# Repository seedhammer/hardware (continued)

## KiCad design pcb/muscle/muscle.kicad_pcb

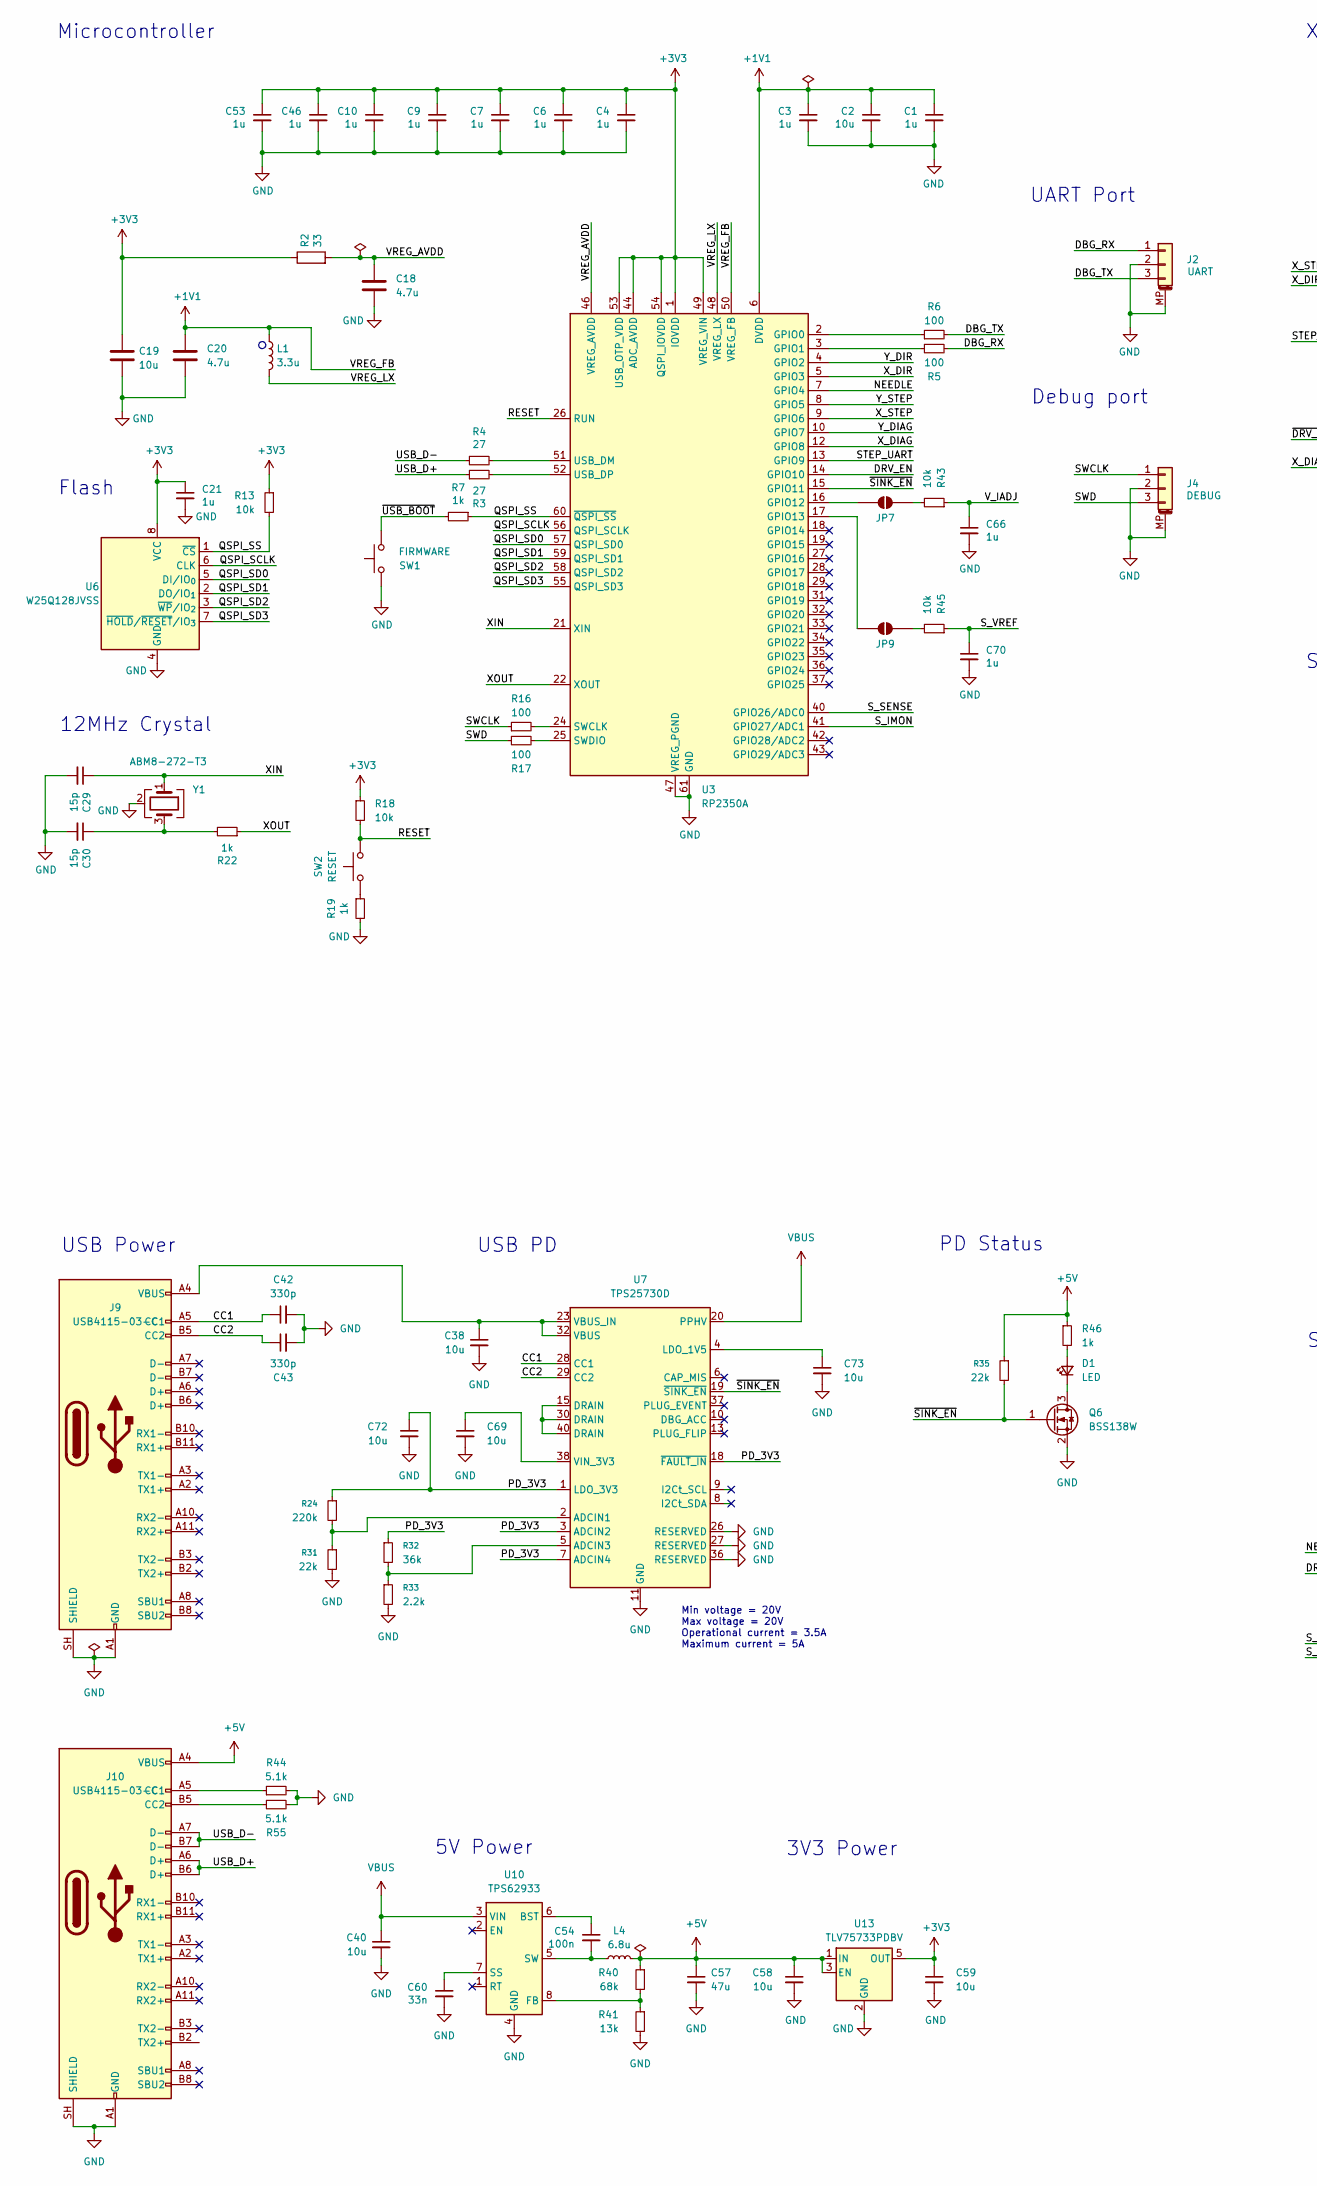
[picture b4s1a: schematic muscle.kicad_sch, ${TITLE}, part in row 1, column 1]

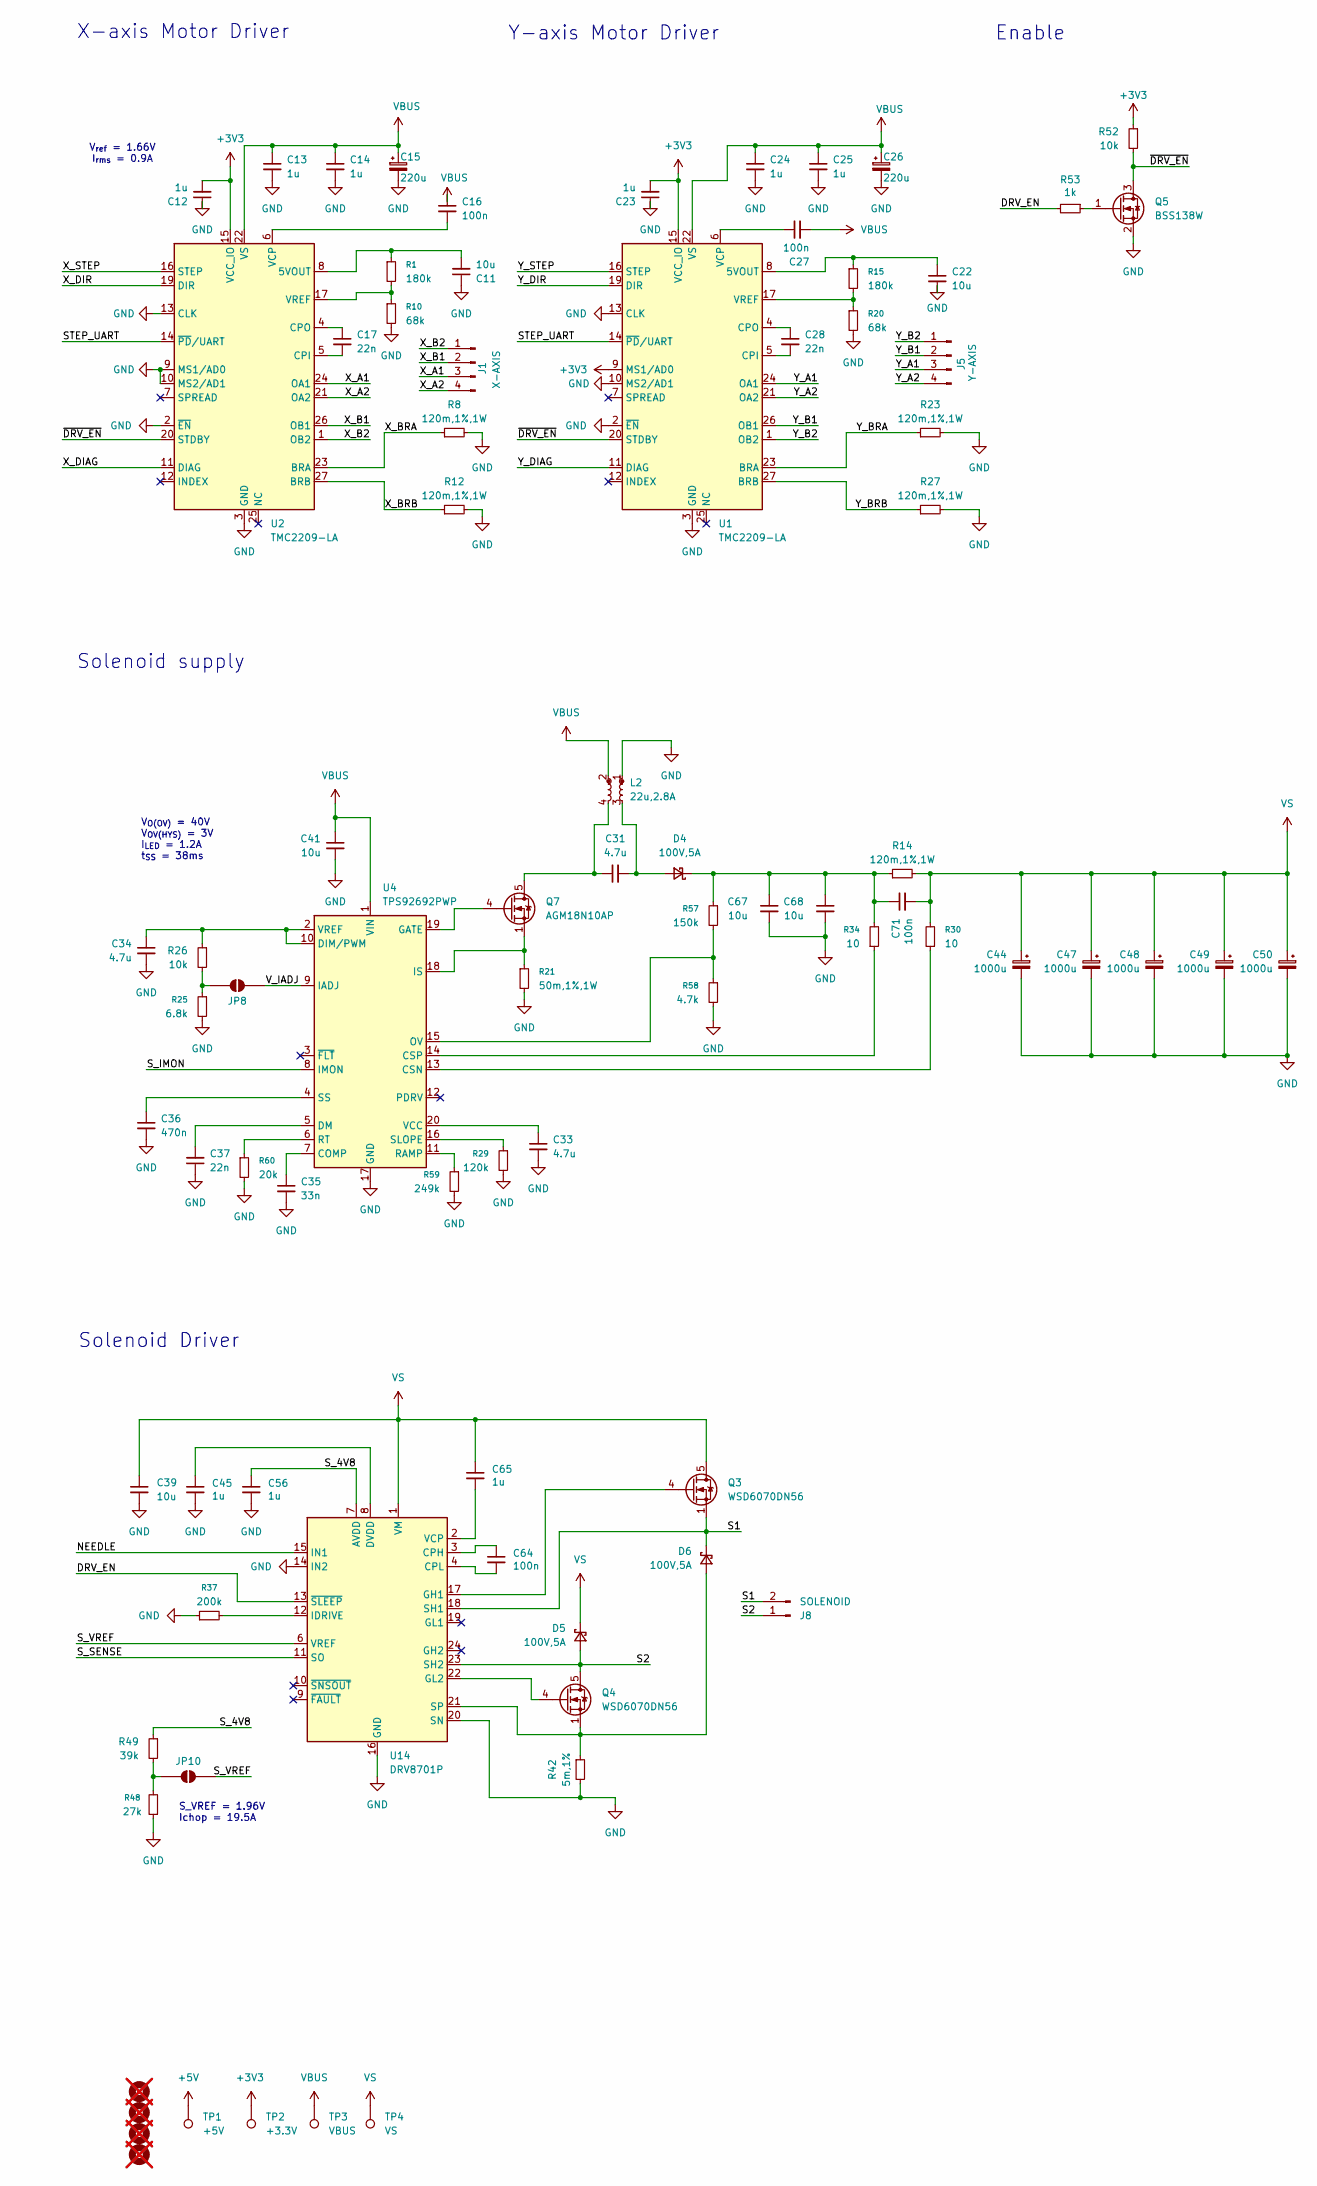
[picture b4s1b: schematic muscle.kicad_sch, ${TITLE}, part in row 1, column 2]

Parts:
C1, C3, C4, C6, C7, C9, C10, C12, C21, C23, C45, C46, C53, C56, C66, C70: 1u; C_0402_1005Metric; LCSC C52923
C2, C11, C22, C58, C59, C69, C72, C73: 10u; C_0402_1005Metric; LCSC C15525
C13, C14, C24, C25, C65: 1u; C_0603_1608Metric; LCSC C15849
C15, C26: 220u; CP_Elec_8x10; LCSC C970697
C16, C27: 100n; C_0603_1608Metric; LCSC C14663
C17, C28, C37: 22n; C_0402_1005Metric; LCSC C1532
C18, C33, C34: 4.7u; C_0402_1005Metric; LCSC C23733
C19: 10u; C_0402_1005Metric_small_pads; LCSC C15525
C20: 4.7u; C_0402_1005Metric_small_pads; LCSC C23733
C29, C30: 15p; C_0402_1005Metric; LCSC C1548
C31: 4.7u; C_1206_3216Metric; LCSC C33546020
C35, C60: 33n; C_0603_1608Metric; LCSC C21117
C36: 470n; C_0603_1608Metric; LCSC C1623
C38, C40, C41: 10u; C_0603_1608Metric; LCSC C96446
C39, C67, C68: 10u; C_1206_3216Metric; LCSC C13585
C42, C43: 330p; C_0603_1608Metric; LCSC C1664
C44, C47, C48, C49, C50: 1000u; CP_Radial_D13.0mm_P5.00mm; LCSC C18104
C54, C64, C71: 100n; C_0402_1005Metric; LCSC C307331
C57: 47u; C_1206_3216Metric; LCSC C96123
D1: LED; LED_0603_1608Metric; LCSC C2290
D4, D5, D6: 100V,5A; D_SMB; LCSC C41410776
H1, H2, H3, H4: MountingHole; MountingHole_3.2mm_M3_DIN965; not fitted
J1, J5: B4B-XH-2(LF)(SN); JST_XH_B4B-XH-A_1x04_P2.50mm_Vertical_Motor; LCSC C57846
J2, J4: ZX-SH1.0-3PLT; JST_SH_BM03B-SRSS-TB_1x03-1MP_P1.00mm_Vertical; LCSC C7430452
J8: B2B-XH-A(LF)(SN); JST_XH_B2B-XH-A_1x02_P2.50mm_Vertical; LCSC C24193
J9, J10: USB4115-03-C; USB_C_Receptacle_GCT_USB4115-03-C; LCSC C5250720
JP7, JP8, JP9, JP10: SolderJumper_2_Bridged; SolderJumper-2_P1.3mm_Open_Pad1.0x1.5mm
L1: 3.3u; L_pol_2016; LCSC C42411119
L2: 22u,2.8A; L_Bourns_SRF1260; LCSC C54563340
L4: 6.8u; L_Vishay_IFSC-1515AH_4x4x1.8mm; LCSC C843301
Q3, Q4: WSD6070DN56; WSD_DFN-8-1EP_6x5mm_P1.27mm_ThermalVias; LCSC C5772651
Q5, Q6: BSS138W; SOT-323_SC-70; LCSC C28646265
Q7: AGM18N10AP; VSON-8_3.3x3.3mm_P0.65mm_NexFET; LCSC C7509649
R1, R15: 180k; R_0603_1608Metric; LCSC C22827
R2: 33; R_0402_1005Metric; LCSC C25105
R3, R4: 27; R_0402_1005Metric; LCSC C25100
R5, R6, R16, R17: 100; R_0402_1005Metric; LCSC C25076
R7, R19, R22, R46, R53: 1k; R_0402_1005Metric; LCSC C11702
R8, R12, R14, R23, R27: 120m,1%,1W; R_1206_3216Metric; LCSC C201309
R10, R20: 68k; R_0402_1005Metric; LCSC C23231
R13, R18, R26, R43, R45, R52: 10k; R_0402_1005Metric; LCSC C25744
R21: 50m,1%,1W; R_1206_3216Metric; LCSC C7467249
R24: 220k; R_0603_1608Metric; LCSC C22961
R25: 6.8k; R_0603_1608Metric; LCSC C23212
R29: 120k; R_0603_1608Metric; LCSC C25808
R30, R34: 10; R_0402_1005Metric; LCSC C25077
R31, R35: 22k; R_0402_1005Metric; LCSC C25768
R32: 36k; R_0603_1608Metric; LCSC C23147
R33: 2.2k; R_0402_1005Metric; LCSC C25879
R37: 200k; R_0402_1005Metric; LCSC C25764
R40: 68k; R_0603_1608Metric; LCSC C23231
R41: 13k; R_0603_1608Metric; LCSC C22797
R42: 5m,1%; R_0805_2012Metric; LCSC C728267
R44, R55: 5.1k; R_0402_1005Metric; LCSC C25905
R48: 27k; R_0603_1608Metric; LCSC C22967
R49: 39k; R_0603_1608Metric; LCSC C23153
R57: 150k; R_0603_1608Metric; LCSC C22807
R58: 4.7k; R_0402_1005Metric; LCSC C25900
R59: 249k; R_0402_1005Metric; LCSC C226368
R60: 20k; R_0402_1005Metric; LCSC C25765
SW1, SW2: TS3425BA; SW_Push_1P1T_NO_Vertical_Wuerth_434133025816; LCSC C2681476
TP1: +5V; TestPoint_Pad_1.5x1.5mm
TP2: +3.3V; TestPoint_Pad_1.5x1.5mm
TP3: VBUS; TestPoint_Pad_1.5x1.5mm
TP4: VS; TestPoint_Pad_1.5x1.5mm
U1, U2: TMC2209-LA; VQFN-28-1EP_5x5mm_P0.5mm_EP3.7x3.7mm_ThermalVias; LCSC C2150710
U3: RP2350A; QFN-60-1EP_7x7mm_P0.4mm_EP3.4x3.4mm_ThermalVias; LCSC C42411118
U4: TPS92692PWP; HTSSOP-20-1EP_4.4x6.5mm_P0.65mm_EP3.4x6.5mm_Mask2.75x3.43mm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; LCSC C111084
U6: W25Q128JVSS; SOIC-8_5.3x5.3mm_P1.27mm; LCSC C97521
U7: TPS25730D; Texas_REF0038A_WQFN-38-2EP_6x4mm_P0.4; LCSC C22438973
U10: TPS62933; SOT-583-8; LCSC C3200405
U13: TLV75733PDBV; SOT-23-5; LCSC C485517
U14: DRV8701P; VQFN-24-1EP_4x4mm_P0.5mm_EP2.45x2.45mm_ThermalVias; LCSC C114178
Y1: ABM8-272-T3; Crystal_SMD_3225-4Pin_3.2x2.5mm; LCSC C20625731

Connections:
+1V1: C1.1, C2.1, C3.1, C20.1, L1.1, U3.6 (DVDD), U3.23 (DVDD), U3.39 (DVDD), U3.50 (VREG_FB)
+3V3: C4.1, C6.1, C7.1, C9.1, C10.1, C12.2, C19.1, C21.1, C23.2, C46.1, C53.1, C59.1, R2.1, R13.1, R18.1, R52.1, TP2.1 (1_1), U1.9 (MS1/AD0), U1.15 (VCC_IO), U2.15 (VCC_IO), U3.1 (IOVDD), U3.11 (IOVDD), U3.20 (IOVDD), U3.30 (IOVDD), U3.38 (IOVDD), U3.44 (ADC_AVDD), U3.45 (IOVDD), U3.49 (VREG_VIN), U3.53 (USB_OTP_VDD), U3.54 (QSPI_IOVDD), U6.8 (VCC), U13.5 (OUT)
+5V: C57.1, C58.1, J10.A4 (VBUS), J10.A9 (VBUS), J10.B4 (VBUS), J10.B9 (VBUS), L4.2, R35.1, R40.1, R46.1, TP1.1 (1_1), U13.1 (IN), U13.3 (EN)
/CC1: C42.1, J9.A5 (CC1), U7.28 (CC1)
/CC2: C43.1, J9.B5 (CC2), U7.29 (CC2)
/DBG_RX: J2.1, R5.2
/DBG_TX: J2.3, R6.2
/DRV_EN: R53.2, U3.14 (GPIO10), U14.13 (~SLEEP)
/NEEDLE: U3.7 (GPIO4), U14.15 (IN1)
/PD_3V3: C72.1, R24.1, R32.1, U7.1 (LDO_3V3), U7.3 (ADCIN2), U7.7 (ADCIN4), U7.18 (~FAULT_IN)
/QSPI_SCLK: U3.56 (QSPI_SCLK), U6.6 (CLK)
/QSPI_SD0: U3.57 (QSPI_SD0), U6.5 (DI/IO_{0})
/QSPI_SD1: U3.59 (QSPI_SD1), U6.2 (DO/IO_{1})
/QSPI_SD2: U3.58 (QSPI_SD2), U6.3 (~WP/IO_{2})
/QSPI_SD3: U3.55 (QSPI_SD3), U6.7 (~HOLD/~RESET/IO_{3})
/QSPI_SS: R7.1, R13.2, U3.60 (~QSPI_SS), U6.1 (~CS)
/RESET: R18.2, SW2.2, U3.26 (RUN)
/S1: D6.1 (K), J8.2, Q3.1 (S), Q3.2 (S), Q3.3 (S), U14.18 (SH1)
/S2: D5.2 (A), J8.1, Q4.5 (D), U14.23 (SH2)
/STEP_UART: U1.14 (~PD/UART), U2.14 (~PD/UART), U3.13 (GPIO9)
/SWCLK: J4.1, R16.1
/SWD: J4.3, R17.1
/S_4V8: C56.1, R49.1, U14.7 (AVDD)
/S_IMON: U3.41 (GPIO27/ADC1), U4.8 (IMON)
/S_SENSE: U3.40 (GPIO26/ADC0), U14.11 (SO)
/S_VREF: C70.1, JP10.1 (A), R45.1, U14.6 (VREF)
/USB_D+: J10.A6 (D+), J10.B6 (D+), R3.1
/USB_D-: J10.A7 (D-), J10.B7 (D-), R4.1
/VREG_AVDD: C18.1, R2.2, U3.46 (VREG_AVDD)
/VREG_LX: L1.2, U3.48 (VREG_LX)
/V_IADJ: C66.1, JP8.1 (A), R43.1, U4.9 (IADJ)
/XIN: C29.1, U3.21 (XIN), Y1.1
/XOUT: R22.1, U3.22 (XOUT)
/X_A1: J1.3, U2.24 (OA1)
/X_A2: J1.4, U2.21 (OA2)
/X_B1: J1.2, U2.26 (OB1)
/X_B2: J1.1, U2.1 (OB2)
/X_BRA: R8.1, U2.23 (BRA)
/X_BRB: R12.1, U2.27 (BRB)
/X_DIAG: U2.11 (DIAG), U3.12 (GPIO8)
/X_DIR: U2.19 (DIR), U3.5 (GPIO3)
/X_STEP: U2.16 (STEP), U3.9 (GPIO6)
/Y_A1: J5.3, U1.24 (OA1)
/Y_A2: J5.4, U1.21 (OA2)
/Y_B1: J5.2, U1.26 (OB1)
/Y_B2: J5.1, U1.1 (OB2)
/Y_BRA: R23.1, U1.23 (BRA)
/Y_BRB: R27.1, U1.27 (BRB)
/Y_DIAG: U1.11 (DIAG), U3.10 (GPIO7)
/Y_DIR: U1.19 (DIR), U3.4 (GPIO2)
/Y_STEP: U1.16 (STEP), U3.8 (GPIO5)
/~DRV_EN: Q5.3 (D), R52.2, U1.20 (STDBY), U2.20 (STDBY)
/~SINK_EN: Q6.1 (G), R35.2, U3.15 (GPIO11), U7.19 (~SINK_EN)
/~USB_BOOT: R7.2, SW1.1
GND: C1.2, C2.2, C3.2, C4.2, C6.2, C7.2, C9.2, C10.2, C11.1, C12.1, C13.2, C14.2, C15.2, C18.2, C19.2, C20.2, C21.2, C22.2, C23.1, C24.2, C25.2, C26.2, C29.2, C30.2, C33.2, C34.2, C35.2, C36.2, C37.1, C38.2, C39.2, C40.2, C41.2, C42.2, C43.2, C44.2, C45.2, C46.2, C47.2, C48.2, C49.2, C50.2, C53.2, C56.2, C57.2, C58.2, C59.2, C60.2, C66.2, C67.2, C68.2, C69.2, C70.2, C72.2, C73.2, J2.2, J2.MP (MountPin), J4.2, J4.MP (MountPin), J9.A1 (GND), J9.A12 (GND), J9.B1 (GND), J9.B12 (GND), J9.SH (SHIELD), J10.A1 (GND), J10.A12 (GND), J10.B1 (GND), J10.B12 (GND), J10.SH (SHIELD), L2.1, Q5.2 (S), Q6.2 (S), R8.2, R10.2, R12.2, R19.2, R20.2, R21.2, R23.2, R25.2, R27.2, R29.2, R31.2, R33.2, R37.1, R41.2, R42.2, R44.2, R48.1, R55.2, R58.2, R59.2, R60.2, SW1.2, U1.2 (~EN), U1.3 (GND), U1.10 (MS2/AD1), U1.13 (CLK), U1.18 (GND), U1.29 (GND), U2.2 (~EN), U2.3 (GND), U2.9 (MS1/AD0), U2.10 (MS2/AD1), U2.13 (CLK), U2.18 (GND), U2.29 (GND), U3.47 (VREG_PGND), U3.61 (GND), U4.17 (GND), U4.21 (GND), U6.4 (GND), U7.11 (GND), U7.12 (GND), U7.14 (GND), U7.16 (GND), U7.17 (GND), U7.26 (RESERVED), U7.27 (RESERVED), U7.31 (GND), U7.34 (GND), U7.36 (RESERVED), U7.39 (GND), U10.4 (GND), U13.2 (GND), U14.5 (GND), U14.14 (IN2), U14.16 (GND), U14.20 (SN), U14.25 (GND), Y1.2 (G), Y1.4 (G)
unnamed: C30.1, R22.2, Y1.3
unnamed: D1.2 (A), R46.2
unnamed: D1.1 (K), Q6.3 (D)
unnamed: C31.2, D4.2 (A), L2.3
unnamed: C67.1, C68.1, C71.1, D4.1 (K), R14.1, R34.2, R57.1
unnamed: D6.2 (A), Q4.1 (S), Q4.2 (S), Q4.3 (S), R42.1, U14.21 (SP)
unnamed: J10.A5 (CC1), R44.1
unnamed: J10.B5 (CC2), R55.1
unnamed: JP7.1 (A), R43.2
unnamed: JP7.2 (B), U3.16 (GPIO12)
unnamed: JP8.2 (B), R25.1, R26.2
unnamed: JP9.1 (A), R45.2
unnamed: JP9.2 (B), U3.17 (GPIO13)
unnamed: JP10.2 (B), R48.2, R49.2
unnamed: Q3.4 (G), U14.17 (GH1)
unnamed: Q4.4 (G), U14.22 (GL2)
unnamed: Q5.1 (G), R53.1
unnamed: C31.1, L2.4, Q7.5 (D)
unnamed: Q7.4 (G), U4.19 (GATE)
unnamed: R19.1, SW2.1
unnamed: C22.1, R15.1, U1.8 (5VOUT)
unnamed: C28.2, U1.5 (CPI)
unnamed: C28.1, U1.4 (CPO)
unnamed: C27.1, U1.6 (VCP)
unnamed: R15.2, R20.1, U1.17 (VREF)
unnamed: C11.2, R1.1, U2.8 (5VOUT)
unnamed: C17.2, U2.5 (CPI)
unnamed: C17.1, U2.4 (CPO)
unnamed: C16.2, U2.6 (VCP)
unnamed: R1.2, R10.1, U2.17 (VREF)
unnamed: R6.1, U3.2 (GPIO0)
unnamed: R5.1, U3.3 (GPIO1)
unnamed: R16.2, U3.24 (SWCLK)
unnamed: R17.2, U3.25 (SWDIO)
unnamed: R4.2, U3.51 (USB_DM)
unnamed: R3.2, U3.52 (USB_DP)
unnamed: C35.1, U4.7 (COMP)
unnamed: R30.1, U4.13 (CSN)
unnamed: R34.1, U4.14 (CSP)
unnamed: C34.1, R26.1, U4.2 (VREF), U4.10 (DIM/PWM)
unnamed: C37.2, U4.5 (DM)
unnamed: Q7.1 (S), Q7.2 (S), Q7.3 (S), R21.1, U4.18 (IS)
unnamed: R57.2, R58.1, U4.15 (OV)
unnamed: R59.1, U4.11 (RAMP)
unnamed: R60.1, U4.6 (RT)
unnamed: R29.1, U4.16 (SLOPE)
unnamed: C36.1, U4.4 (SS)
unnamed: C33.1, U4.20 (VCC)
unnamed: R24.2, R31.1, U7.2 (ADCIN1)
unnamed: R32.2, R33.1, U7.5 (ADCIN3)
unnamed: U7.15 (DRAIN), U7.30 (DRAIN), U7.40 (DRAIN)
unnamed: C73.1, U7.4 (LDO_1V5)
unnamed: C38.1, J9.A4 (VBUS), J9.A9 (VBUS), J9.B4 (VBUS), J9.B9 (VBUS), U7.23 (VBUS_IN), U7.32 (VBUS)
unnamed: C69.1, U7.38 (VIN_3V3)
unnamed: C54.1, U10.6 (BST)
unnamed: R40.2, R41.1, U10.8 (FB)
unnamed: C60.1, U10.7 (SS)
unnamed: C54.2, L4.1, U10.5 (SW)
unnamed: C64.1, U14.3 (CPH)
unnamed: C64.2, U14.4 (CPL)
unnamed: C45.1, U14.8 (DVDD)
unnamed: R37.2, U14.12 (IDRIVE)
unnamed: C65.2, U14.2 (VCP)
VBUS: C13.1, C14.1, C15.1, C16.1, C24.1, C25.1, C26.1, C27.2, C40.1, C41.1, L2.2, TP3.1 (1_1), U1.22 (VS), U1.28 (VS), U2.22 (VS), U2.28 (VS), U4.1 (VIN), U7.20 (PPHV), U10.3 (VIN)
VS: C39.1, C44.1, C47.1, C48.1, C49.1, C50.1, C65.1, C71.2, D5.1 (K), Q3.5 (D), R14.2, R30.2, TP4.1 (1_1), U14.1 (VM)

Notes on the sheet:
S_VREF = 1.96V Ichop = 19.5A
Solenoid supply
UART Port
USB Power
V_{O(OV)} = 40V V_{OV(HYS)} = 3V I_{LED} = 1.2A t_{SS} = 38ms
X-axis Motor Driver
Solenoid Driver
USB PD
5V Power
Debug port
V_{ref} = 1.66V I_{rms} = 0.9A
Y-axis Motor Driver
Min voltage = 20V Max voltage = 20V Operational current = 3.5A Maximum current = 5A
Microcontroller
12MHz Crystal
3V3 Power
PD Status
Flash
Enable

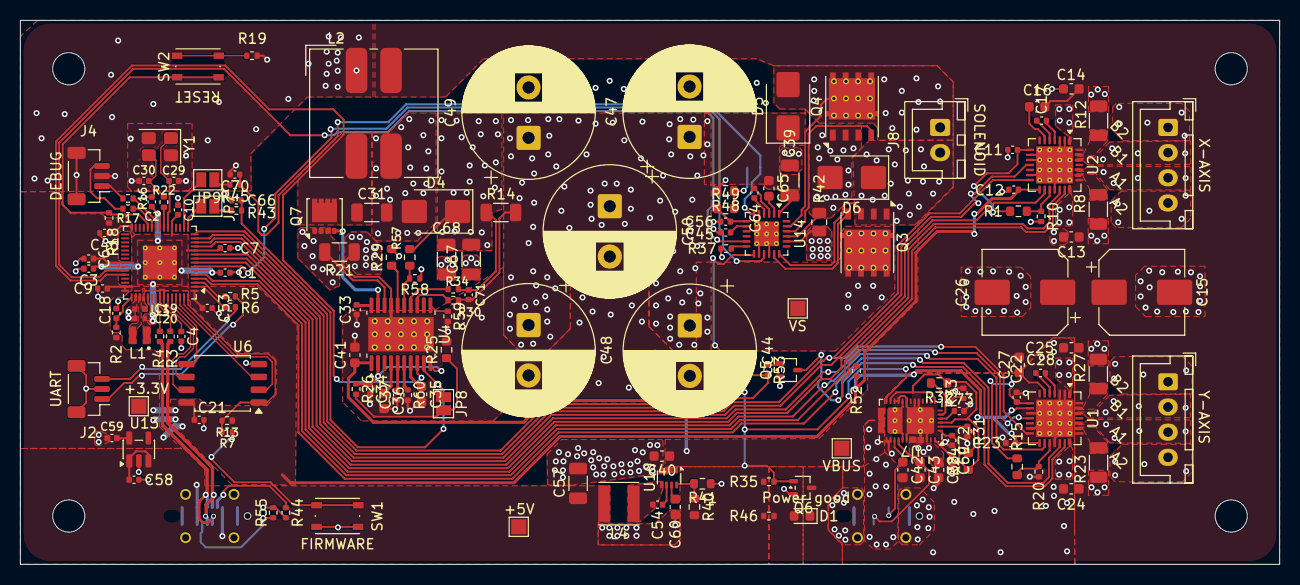
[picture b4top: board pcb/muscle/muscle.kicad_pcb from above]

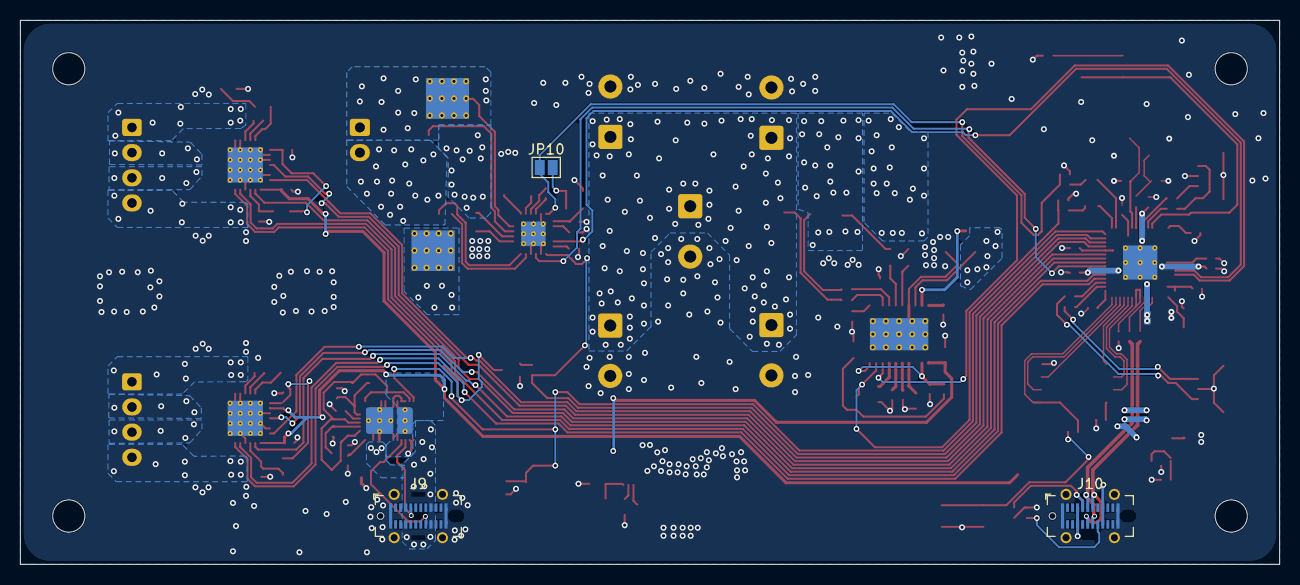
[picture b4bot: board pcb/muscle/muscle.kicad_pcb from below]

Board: 4 copper layers, 125.0 x 54.0 mm, 156 parts (3 on the bottom side), 120 nets.

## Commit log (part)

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2026-02-13 pcb: allow VBUS to drop to 0V during power cycles
    When the external USB PD supply power cycles the board, we keep the
    MCU and LCD powered for a few seconds with charge from the capacitor bank.
    However, the 2 MOSFETs acting as level shifters for USB PD I2C communication
    leaks voltage of ~1V to the I2C ports of the USB PD controller, which
    leaks through to VBUS.
    Some supplies refuse to complete the power cycle as long as there is any
2026-02-13 pcb: configure USB PD controller to ask for 20V at initialization
    The capacitor bank should always be charged to a higher voltage to
    be ready to withstand USB PD charger power cycles.
    The FA02 variant of the AP33772S controller can ask for a higher voltage
    at startup.
2026-02-14 pcb: move I2C level shifter closer to the peripheral
2026-02-20 pcb: replace the linear LCD backlight driver with a buck driver
    We need to conserve as much power as possible for the capacitor bank to
    keep the MCU and LCD powered during USB PD power cycles. Using a buck
    driver saves ~30% power for the most power hungry component, the
    LCD backlight.
2026-02-26 pcb: improve heating and widen VM zones
2026-03-26 pcb: upgrade to KiCAD 10
2026-03-28 pcb: fix the solenoid current limit Ichop 10.3A
2026-03-30 cad: update all files for production
2026-04-03 cad: add stepper motor specification
2026-04-08 pcb: replace AL8861WT with AL8861Y
2026-04-09 pcb: replace stepper plugs and 3Ω resistors
2026-05-05 pcb: replace TMC2226 with TMC2209
2026-05-24 pcb: replace out-of-stock 680pF capacitors
2026-06-18 pcb: remove LED lighting
    LED lighting is pretty, but useless for our purposes.
